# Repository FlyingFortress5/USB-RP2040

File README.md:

# USB-RP2040-DEVB
A RP2040 powered mini dev board. It has 2 GPIO pins, and is intended mainly for scripted HID emulation.

## Features

 - Light BOM
 - extra small size
 - male usb-c plug

## BOM

| Footprint                                   | Designation       | Quantity |   |   |
|---------------------------------------------|-------------------|----------|---|---|
| USB_C_Plug_Molex_105444                     | USB_C_Plug_USB2.0 | 1        |   |   |
| C_0402_1005Metric                           | 0.1uF             | 10       |   |   |
| Winbond_USON-8-1EP_3x2mm_P0.5mm_EP0.2x1.6mm | W25Q16JVZPIQ_TR   | 1        |   |   |
| SOT95P237X112-3N                            | MCP1700T-3302E_TT | 1        |   |   |
| SW_Push_1P1T-SH_NO_CK_KMR2xxG               | SW_Push           | 1        |   |   |
| PinHeader_1x03_P1.00mm_Vertical             | Conn_01x03        | 1        |   |   |
| Crystal_SMD_3225-4Pin_3.2x2.5mm             | 12 MHz            | 1        |   |   |
| QFN-56-1EP_7x7mm_P0.4mm_EP3.2x3.2mm         | RP2040            | 1        |   |   |
| R_0402_1005Metric                           | 10K               | 1        |   |   |
| R_0402_1005Metric                           | 1K                | 2        |   |   |
| R_0402_1005Metric                           | 27                | 2        |   |   |
| R_0402_1005Metric                           | 5.1K              | 2        |   |   |
| C_0402_1005Metric                           | 15pF              | 2        |   |   |
| C_0603_1608Metric_Pad1.08x0.95mm_HandSolder | 10uF              | 2        |   |   |
| C_0402_1005Metric                           | 1uF               | 2        |   |   |

## Case
A simple friction fit case

## Images

## Pinout

The pins on the header from top to bottom are:
 - GPIO0
 - GPIO15
 - GND
 The button enters BOOTSEL

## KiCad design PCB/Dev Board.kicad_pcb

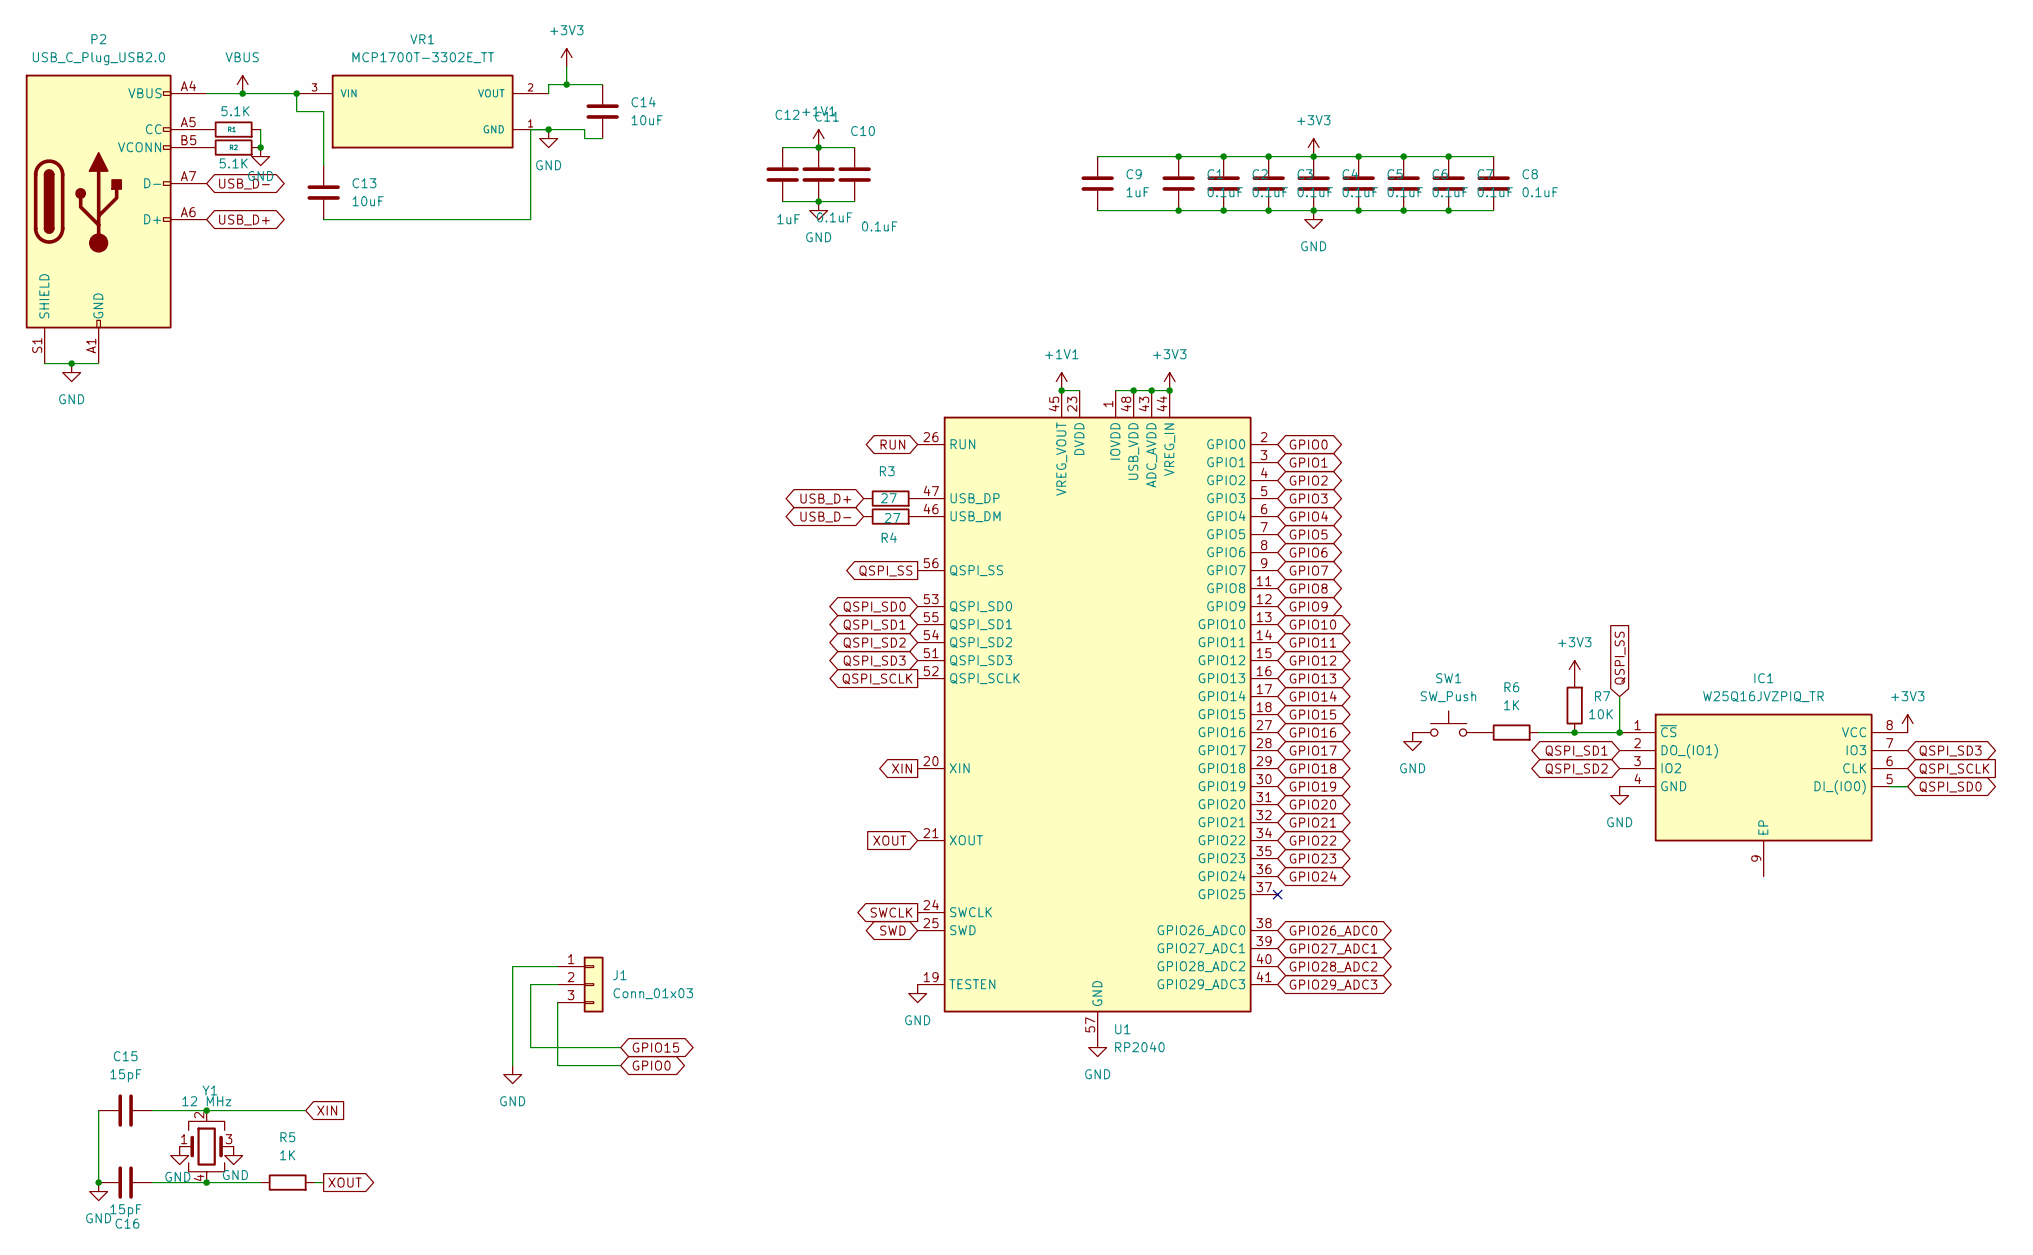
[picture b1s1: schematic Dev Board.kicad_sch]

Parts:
C1, C2, C3, C4, C5, C6, C7, C8, C10, C11: 0.1uF; C_0402_1005Metric
C9, C12: 1uF; C_0402_1005Metric
C13, C14: 10uF; C_0603_1608Metric_Pad1.08x0.95mm_HandSolder
C15, C16: 15pF; C_0402_1005Metric
IC1: W25Q16JVZPIQ_TR; Winbond_USON-8-1EP_3x2mm_P0.5mm_EP0.2x1.6mm; Manufacturer_Part_Number W25Q16JVZPIQ TR
J1: Conn_01x03; PinHeader_1x03_P1.00mm_Vertical
P2: USB_C_Plug_USB2.0; USB_C_Plug_Molex_105444
R1, R2: 5.1K; R_0402_1005Metric
R3, R4: 27; R_0402_1005Metric
R5, R6: 1K; R_0402_1005Metric
R7: 10K; R_0402_1005Metric
SW1: SW_Push; SW_Push_1P1T-SH_NO_CK_KMR2xxG
U1: RP2040; QFN-56-1EP_7x7mm_P0.4mm_EP3.2x3.2mm
VR1: MCP1700T-3302E_TT; SOT95P237X112-3N; PARTREV E
Y1: 12 MHz; Crystal_SMD_3225-4Pin_3.2x2.5mm

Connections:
+1V1: C10.1, C11.1, C12.1, U1.23 (DVDD), U1.45 (VREG_VOUT), U1.50 (DVDD)
+3V3: C1.1, C2.1, C3.1, C4.1, C5.1, C6.1, C7.1, C8.1, C9.1, C14.1, IC1.8 (VCC), R7.2, U1.1 (IOVDD), U1.10 (IOVDD), U1.22 (IOVDD), U1.33 (IOVDD), U1.42 (IOVDD), U1.43 (ADC_AVDD), U1.44 (VREG_IN), U1.48 (USB_VDD), U1.49 (IOVDD), VR1.2 (VOUT)
GND: C1.2, C2.2, C3.2, C4.2, C5.2, C6.2, C7.2, C8.2, C9.2, C10.2, C11.2, C12.2, C13.2, C14.2, C15.1, C16.1, IC1.4 (GND), J1.1, P2.A1 (GND), P2.A12 (GND), P2.B1 (GND), P2.B12 (GND), P2.S1 (SHIELD), R1.2, R2.2, SW1.1, U1.19 (TESTEN), U1.57 (GND), VR1.1 (GND), Y1.1, Y1.3
GPIO0: J1.3, U1.2 (GPIO0)
GPIO1: U1.3 (GPIO1)
GPIO2: U1.4 (GPIO2)
GPIO3: U1.5 (GPIO3)
GPIO4: U1.6 (GPIO4)
GPIO5: U1.7 (GPIO5)
GPIO6: U1.8 (GPIO6)
GPIO7: U1.9 (GPIO7)
GPIO8: U1.11 (GPIO8)
GPIO9: U1.12 (GPIO9)
GPIO10: U1.13 (GPIO10)
GPIO11: U1.14 (GPIO11)
GPIO12: U1.15 (GPIO12)
GPIO13: U1.16 (GPIO13)
GPIO14: U1.17 (GPIO14)
GPIO15: J1.2, U1.18 (GPIO15)
GPIO16: U1.27 (GPIO16)
GPIO17: U1.28 (GPIO17)
GPIO18: U1.29 (GPIO18)
GPIO19: U1.30 (GPIO19)
GPIO20: U1.31 (GPIO20)
GPIO21: U1.32 (GPIO21)
GPIO22: U1.34 (GPIO22)
GPIO23: U1.35 (GPIO23)
GPIO24: U1.36 (GPIO24)
GPIO26_ADC0: U1.38 (GPIO26_ADC0)
GPIO27_ADC1: U1.39 (GPIO27_ADC1)
GPIO28_ADC2: U1.40 (GPIO28_ADC2)
GPIO29_ADC3: U1.41 (GPIO29_ADC3)
unnamed: C16.2, R5.1, Y1.4
unnamed: P2.A5 (CC), R1.1
unnamed: P2.B5 (VCONN), R2.1
unnamed: R6.1, SW1.2
unnamed: R4.2, U1.46 (USB_DM)
unnamed: R3.2, U1.47 (USB_DP)
QSPI_SCLK: IC1.6 (CLK), U1.52 (QSPI_SCLK)
QSPI_SD0: IC1.5 (DI_(IO0)), U1.53 (QSPI_SD0)
QSPI_SD1: IC1.2 (DO_(IO1)), U1.55 (QSPI_SD1)
QSPI_SD2: IC1.3 (IO2), U1.54 (QSPI_SD2)
QSPI_SD3: IC1.7 (IO3), U1.51 (QSPI_SD3)
QSPI_SS: IC1.1 (~CS), R6.2, R7.1, U1.56 (QSPI_SS)
RUN: U1.26 (RUN)
SWCLK: U1.24 (SWCLK)
SWD: U1.25 (SWD)
USB_D+: P2.A6 (D+), R3.1
USB_D-: P2.A7 (D-), R4.1
VBUS: C13.1, P2.A4 (VBUS), P2.A9 (VBUS), P2.B4 (VBUS), P2.B9 (VBUS), VR1.3 (VIN)
XIN: C15.2, U1.20 (XIN), Y1.2
XOUT: R5.2, U1.21 (XOUT)

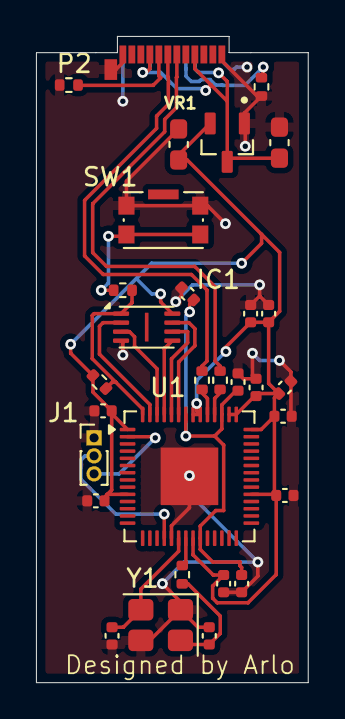
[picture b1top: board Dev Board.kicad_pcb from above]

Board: 2 copper layers, 15.1 x 35.9 mm, 30 parts (0 on the bottom side), 22 nets.

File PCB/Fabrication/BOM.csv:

"Id";"Designator";"Footprint";"Quantity";"Designation";"Supplier and ref";
1;"P2";"USB_C_Plug_Molex_105444";1;"USB_C_Plug_USB2.0";;;
2;"C10,C11,C8,C7,C6,C5,C4,C3,C2,C1";"C_0402_1005Metric";10;"0.1uF";;;
3;"IC1";"Winbond_USON-8-1EP_3x2mm_P0.5mm_EP0.2x1.6mm";1;"W25Q16JVZPIQ_TR";;;
4;"VR1";"SOT95P237X112-3N";1;"MCP1700T-3302E_TT";;;
5;"SW1";"SW_Push_1P1T-SH_NO_CK_KMR2xxG";1;"SW_Push";;;
6;"J1";"PinHeader_1x03_P1.00mm_Vertical";1;"Conn_01x03";;;
7;"Y1";"Crystal_SMD_3225-4Pin_3.2x2.5mm";1;"12 MHz";;;
8;"U1";"QFN-56-1EP_7x7mm_P0.4mm_EP3.2x3.2mm";1;"RP2040";;;
9;"R7";"R_0402_1005Metric";1;"10K";;;
10;"R6,R5";"R_0402_1005Metric";2;"1K";;;
11;"R4,R3";"R_0402_1005Metric";2;"27";;;
12;"R2,R1";"R_0402_1005Metric";2;"5.1K";;;
13;"C16,C15";"C_0402_1005Metric";2;"15pF";;;
14;"C14,C13";"C_0603_1608Metric_Pad1.08x0.95mm_HandSolder";2;"10uF";;;
15;"C12,C9";"C_0402_1005Metric";2;"1uF";;;

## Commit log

2025-12-05 Edit Readme and add PCB files and images
2025-12-05 Edit Readme
2025-12-06 Added case
2025-12-06 Added gerber drill files
2025-12-06 Rename Dev Board.csv to BOM.csv
